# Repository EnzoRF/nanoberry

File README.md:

# Project Nanoberry*
(*) Provisional name until we find anything better

# What is it?
Nanoberry is a **single-board computer** capable of running **Linux**. It is built around the **i. MX 6 UltraLite** system-on-chip from NXP. It's **open-source hardware**, its design files are made in **KiCad** and it's free for everyone to produce it, sell it, modify it, and sell modified versions of it.

It is designed to be similar to the very popular **Raspberry PI**, with the same board size and connectors located in the same side. There are some differences, most notably it does not have HDMI output.

The goal is to have a small computer that everybody can modify according to their needs. All the electronics components can be purchased from electronics distributors and its operation is well documented by the manufacturers. This is the main difference with Raspberry PI.

All components are also available in industrial grade, for projects that require extra reliabilty with an increase in the cost. 

## License

You can modify this project and manufacture it, sell it for money, but you have to let me know.

    Nanoberry (provisional name). Open source single board computer.
    Copyright (C) 2020  vpecanins

    This program is free software: you can redistribute it and/or modify
    it under the terms of the GNU General Public License as published by
    the Free Software Foundation, either version 3 of the License, or
    (at your option) any later version.

    This program is distributed in the hope that it will be useful,
    but WITHOUT ANY WARRANTY; without even the implied warranty of
    MERCHANTABILITY or FITNESS FOR A PARTICULAR PURPOSE.  See the
    GNU General Public License for more details.

    You should have received a copy of the GNU General Public License
    along with this program.  If not, see <https://www.gnu.org/licenses/>.

 [GNU GENERAL PUBLIC LICENSE v3](https://www.gnu.org/licenses/gpl-3.0.en.html)

## Specifications

 - System-on-chip NXP i.MX 6 ULL:
	 - ARM Cortex A7 CPU at 900 MHz
	 - Yocto Linux Operating System
 - 4 layer PCB project made in KiCAD
 - Flash memory for program & data storage:
	 - Micro-SD card slot
	 - Onboard QSPI Flash (2 packages) for Bootloader and small OS
 - RAM memory: DDR3L one package
 - Display: 24-bit parallel RGB through bottom connector. (eLCDIF peripheral from i.MX6ULL)
	 - HDMI output would be nice but was discarded due to licensing costs and requirement of NDA does not follow the philosophy of this project.
 - Crypto memory A71CH from NXP to store private/public keys, just for fun because it's cheap.
 - PMIC PF1550 from NXP to generate needed voltages for CPU & memory
 - Ethernet 10/100 one port
 - USB to Serial port bridge for debugging and access Linux console
 - USB OTG port to implement special functions by i.MX (for example Mass Storage Device)
 - 4 port USB HUB to connect keyboard, mouse & other USB devices
 - Battery holder for RTC
 - Many I2C, SPI, I2S, UART, GPIO available through pin headers

## Block Diagram

## Status of the project

Hardware design is 99% done and has not been tested. We have based the design around a reference design from NXP. The most critical part of the layout, that is DDR3 routing, has been copied straight away from reference design.

Up to now this project has been brought up by a single person. This project cannot succeed without a team of people working on it. We need to check the schematics, refine layout, bring up the first prototype, boot Linux on it. If you are interested let me know.

We are also looking for funding/sponsors. NXP, we are using a lot of your chips here, if you are interested please show up now.

## BOM (critical components)

 1. MCIMX6Y2CVM08AB - System on chip Cortex A9 (NXP)
 2. MC34PF1550A6EP - PMIC (NXP)
 3. W634GU6MB - 512 MByte RAM (Winbond)
 4. CP2102N-A01-GQFN20 (SiLabs)
 5. LAN8720A-CP (Microchip)
 6. USB2514B (Microchip)

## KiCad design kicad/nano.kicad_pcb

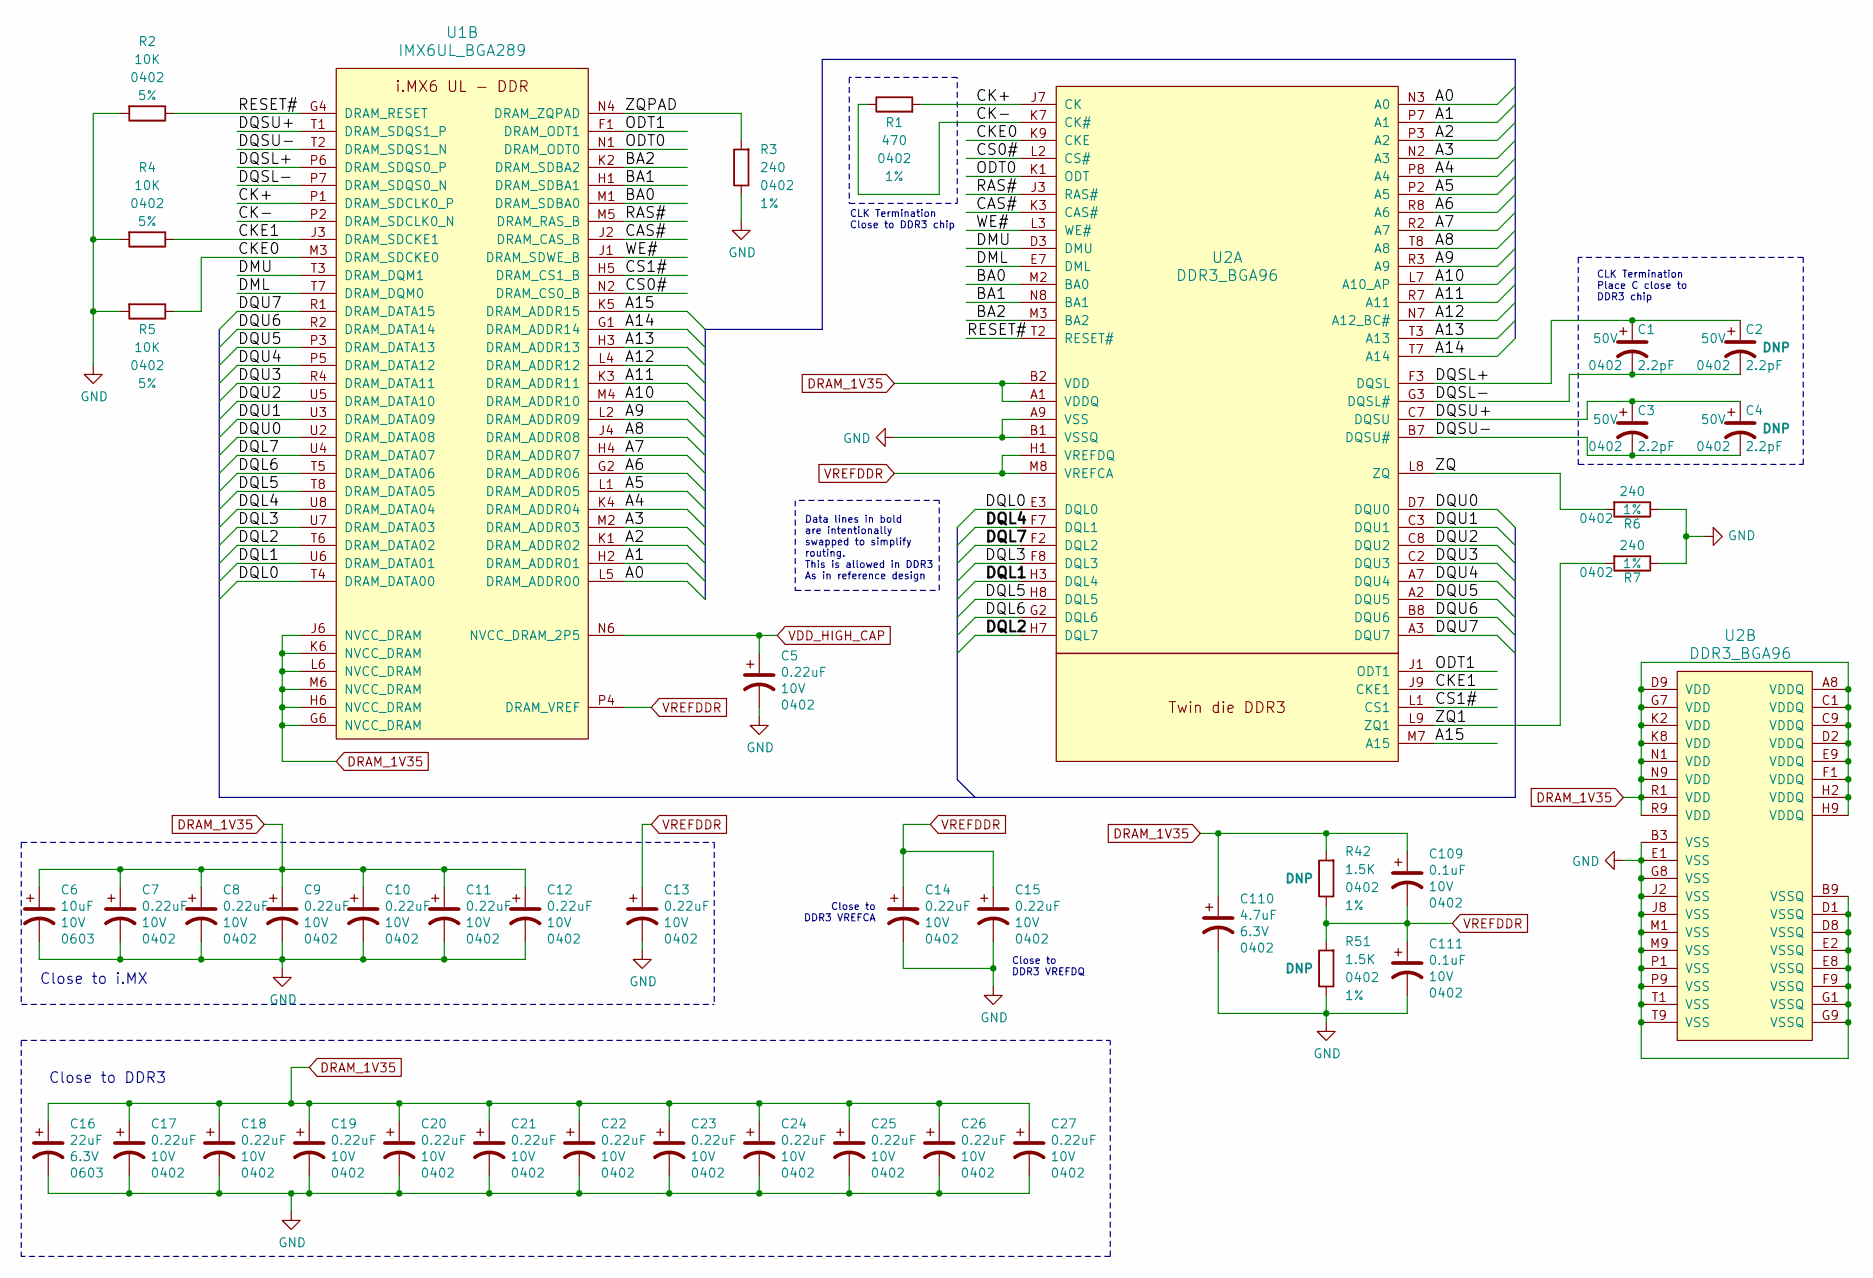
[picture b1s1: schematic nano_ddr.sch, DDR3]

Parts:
C1, C2, C3, C4: 2.2pF; C_0402_narrow; Voltage 50V
C5, C7, C8, C9, C10, C11, C12, C13, C14, C15, C17, C18, C19, C20, C21, C22, C23, C24, C25, C26, C27: 0.22uF; C_0402_narrow; Voltage 10V
C6: 10uF; C_0603_narrow; Voltage 10V
C16: 22uF; C_0603_narrow; Voltage 6.3V
C109, C111: 0.1uF; C_0402_narrow; Voltage 10V
C110: 4.7uF; C_0402_narrow; Voltage 6.3V
R1: 470; R_0402_narrow; Tolerance 1%
R2, R4, R5: 10K; R_0402_narrow; Tolerance 5%
R3, R6, R7: 240; R_0402_narrow; Tolerance 1%
R42, R51: 1.5K; R_0402_narrow; Tolerance 1%
U1: IMX6UL_BGA289
U2: DDR3_BGA96

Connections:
/DDR/A0: U1.L5 (DRAM_ADDR00), U2.N3 (A0)
/DDR/A1: U1.H2 (DRAM_ADDR01), U2.P7 (A1)
/DDR/A2: U1.K1 (DRAM_ADDR02), U2.P3 (A2)
/DDR/A3: U1.M2 (DRAM_ADDR03), U2.N2 (A3)
/DDR/A4: U1.K4 (DRAM_ADDR04), U2.P8 (A4)
/DDR/A5: U1.L1 (DRAM_ADDR05), U2.P2 (A5)
/DDR/A6: U1.G2 (DRAM_ADDR06), U2.R8 (A6)
/DDR/A7: U1.H4 (DRAM_ADDR07), U2.R2 (A7)
/DDR/A8: U1.J4 (DRAM_ADDR08), U2.T8 (A8)
/DDR/A9: U1.L2 (DRAM_ADDR09), U2.R3 (A9)
/DDR/A10: U1.M4 (DRAM_ADDR10), U2.L7 (A10_AP)
/DDR/A11: U1.K3 (DRAM_ADDR11), U2.R7 (A11)
/DDR/A12: U1.L4 (DRAM_ADDR12), U2.N7 (A12_BC#)
/DDR/A13: U1.H3 (DRAM_ADDR13), U2.T3 (A13)
/DDR/A14: U1.G1 (DRAM_ADDR14), U2.T7 (A14)
/DDR/A15: U1.K5 (DRAM_ADDR15), U2.M7 (A15)
/DDR/BA0: U1.M1 (DRAM_SDBA0), U2.M2 (BA0)
/DDR/BA1: U1.H1 (DRAM_SDBA1), U2.N8 (BA1)
/DDR/BA2: U1.K2 (DRAM_SDBA2), U2.M3 (BA2)
/DDR/CAS#: U1.J2 (DRAM_CAS_B), U2.K3 (CAS#)
/DDR/CK+: R1.2, U1.P1 (DRAM_SDCLK0_P), U2.J7 (CK)
/DDR/CK-: R1.1, U1.P2 (DRAM_SDCLK0_N), U2.K7 (CK#)
/DDR/CKE0: R5.1, U1.M3 (DRAM_SDCKE0), U2.K9 (CKE)
/DDR/CKE1: R4.1, U1.J3 (DRAM_SDCKE1), U2.J9 (CKE1)
/DDR/CS0#: U1.N2 (DRAM_CS0_B), U2.L2 (CS#)
/DDR/CS1#: U1.H5 (DRAM_CS1_B), U2.L1 (CS1)
/DDR/DML: U1.T7 (DRAM_DQM0), U2.E7 (DML)
/DDR/DMU: U1.T3 (DRAM_DQM1), U2.D3 (DMU)
/DDR/DQL0: U1.T4 (DRAM_DATA00), U2.E3 (DQL0)
/DDR/DQL1: U1.U6 (DRAM_DATA01), U2.H3 (DQL4)
/DDR/DQL2: U1.T6 (DRAM_DATA02), U2.H7 (DQL7)
/DDR/DQL3: U1.U7 (DRAM_DATA03), U2.F8 (DQL3)
/DDR/DQL4: U1.U8 (DRAM_DATA04), U2.F7 (DQL1)
/DDR/DQL5: U1.T8 (DRAM_DATA05), U2.H8 (DQL5)
/DDR/DQL6: U1.T5 (DRAM_DATA06), U2.G2 (DQL6)
/DDR/DQL7: U1.U4 (DRAM_DATA07), U2.F2 (DQL2)
/DDR/DQSL+: C1.1, C2.1, U1.P6 (DRAM_SDQS0_P), U2.F3 (DQSL)
/DDR/DQSL-: C1.2, C2.2, U1.P7 (DRAM_SDQS0_N), U2.G3 (DQSL#)
/DDR/DQSU+: C3.1, C4.1, U1.T1 (DRAM_SDQS1_P), U2.C7 (DQSU)
/DDR/DQSU-: C3.2, C4.2, U1.T2 (DRAM_SDQS1_N), U2.B7 (DQSU#)
/DDR/DQU0: U1.U2 (DRAM_DATA08), U2.D7 (DQU0)
/DDR/DQU1: U1.U3 (DRAM_DATA09), U2.C3 (DQU1)
/DDR/DQU2: U1.U5 (DRAM_DATA10), U2.C8 (DQU2)
/DDR/DQU3: U1.R4 (DRAM_DATA11), U2.C2 (DQU3)
/DDR/DQU4: U1.P5 (DRAM_DATA12), U2.A7 (DQU4)
/DDR/DQU5: U1.P3 (DRAM_DATA13), U2.A2 (DQU5)
/DDR/DQU6: U1.R2 (DRAM_DATA14), U2.B8 (DQU6)
/DDR/DQU7: U1.R1 (DRAM_DATA15), U2.A3 (DQU7)
/DDR/ODT0: U1.N1 (DRAM_ODT0), U2.K1 (ODT)
/DDR/ODT1: U1.F1 (DRAM_ODT1), U2.J1 (ODT1)
/DDR/RAS#: U1.M5 (DRAM_RAS_B), U2.J3 (RAS#)
/DDR/RESET#: R2.1, U1.G4 (DRAM_RESET), U2.T2 (RESET#)
/DDR/WE#: U1.J1 (DRAM_SDWE_B), U2.L3 (WE#)
/DDR/ZQ: R6.2, U2.L8 (ZQ)
/DDR/ZQ1: R7.2, U2.L9 (ZQ1)
/DDR/ZQPAD: R3.2, U1.N4 (DRAM_ZQPAD)
DRAM_1V35: C6.1, C7.1, C8.1, C9.1, C10.1, C11.1, C12.1, C16.1, C17.1, C18.1, C19.1, C20.1, C21.1, C22.1, C23.1, C24.1, C25.1, C26.1, C27.1, C109.1, C110.1, R42.2, U1.G6 (NVCC_DRAM), U1.H6 (NVCC_DRAM), U1.J6 (NVCC_DRAM), U1.K6 (NVCC_DRAM), U1.L6 (NVCC_DRAM), U1.M6 (NVCC_DRAM), U2.A1 (VDDQ), U2.A8 (VDDQ), U2.B2 (VDD), U2.C1 (VDDQ), U2.C9 (VDDQ), U2.D2 (VDDQ), U2.D9 (VDD), U2.E9 (VDDQ), U2.F1 (VDDQ), U2.G7 (VDD), U2.H2 (VDDQ), U2.H9 (VDDQ), U2.K2 (VDD), U2.K8 (VDD), U2.N1 (VDD), U2.N9 (VDD), U2.R1 (VDD), U2.R9 (VDD); also elsewhere on the board
GND: C5.2, C6.2, C7.2, C8.2, C9.2, C10.2, C11.2, C12.2, C13.2, C14.2, C15.2, C16.2, C17.2, C18.2, C19.2, C20.2, C21.2, C22.2, C23.2, C24.2, C25.2, C26.2, C27.2, C110.2, C111.2, R2.2, R3.1, R4.2, R5.2, R6.1, R7.1, R51.1, U2.A9 (VSS), U2.B1 (VSSQ), U2.B3 (VSS), U2.B9 (VSSQ), U2.D1 (VSSQ), U2.D8 (VSSQ), U2.E1 (VSS), U2.E2 (VSSQ), U2.E8 (VSSQ), U2.F9 (VSSQ), U2.G1 (VSSQ), U2.G8 (VSS), U2.G9 (VSSQ), U2.J2 (VSS), U2.J8 (VSS), U2.M1 (VSS), U2.M9 (VSS), U2.P1 (VSS), U2.P9 (VSS), U2.T1 (VSS), U2.T9 (VSS); also elsewhere on the board
VDD_HIGH_CAP: C5.1, U1.N6 (NVCC_DRAM_2P5); also elsewhere on the board
VREFDDR: C13.1, C14.1, C15.1, C109.2, C111.1, R42.1, R51.2, U1.P4 (DRAM_VREF), U2.H1 (VREFDQ), U2.M8 (VREFCA); also elsewhere on the board

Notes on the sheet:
CLK Termination Close to DDR3 chip
CLK Termination Place C close to DDR3 chip
Close to i.MX
Close to DDR3
Close to DDR3 VREFCA
Data lines in bold are intentionally swapped to simplify routing. This is allowed in DDR3 As in reference design
Close to DDR3 VREFDQ

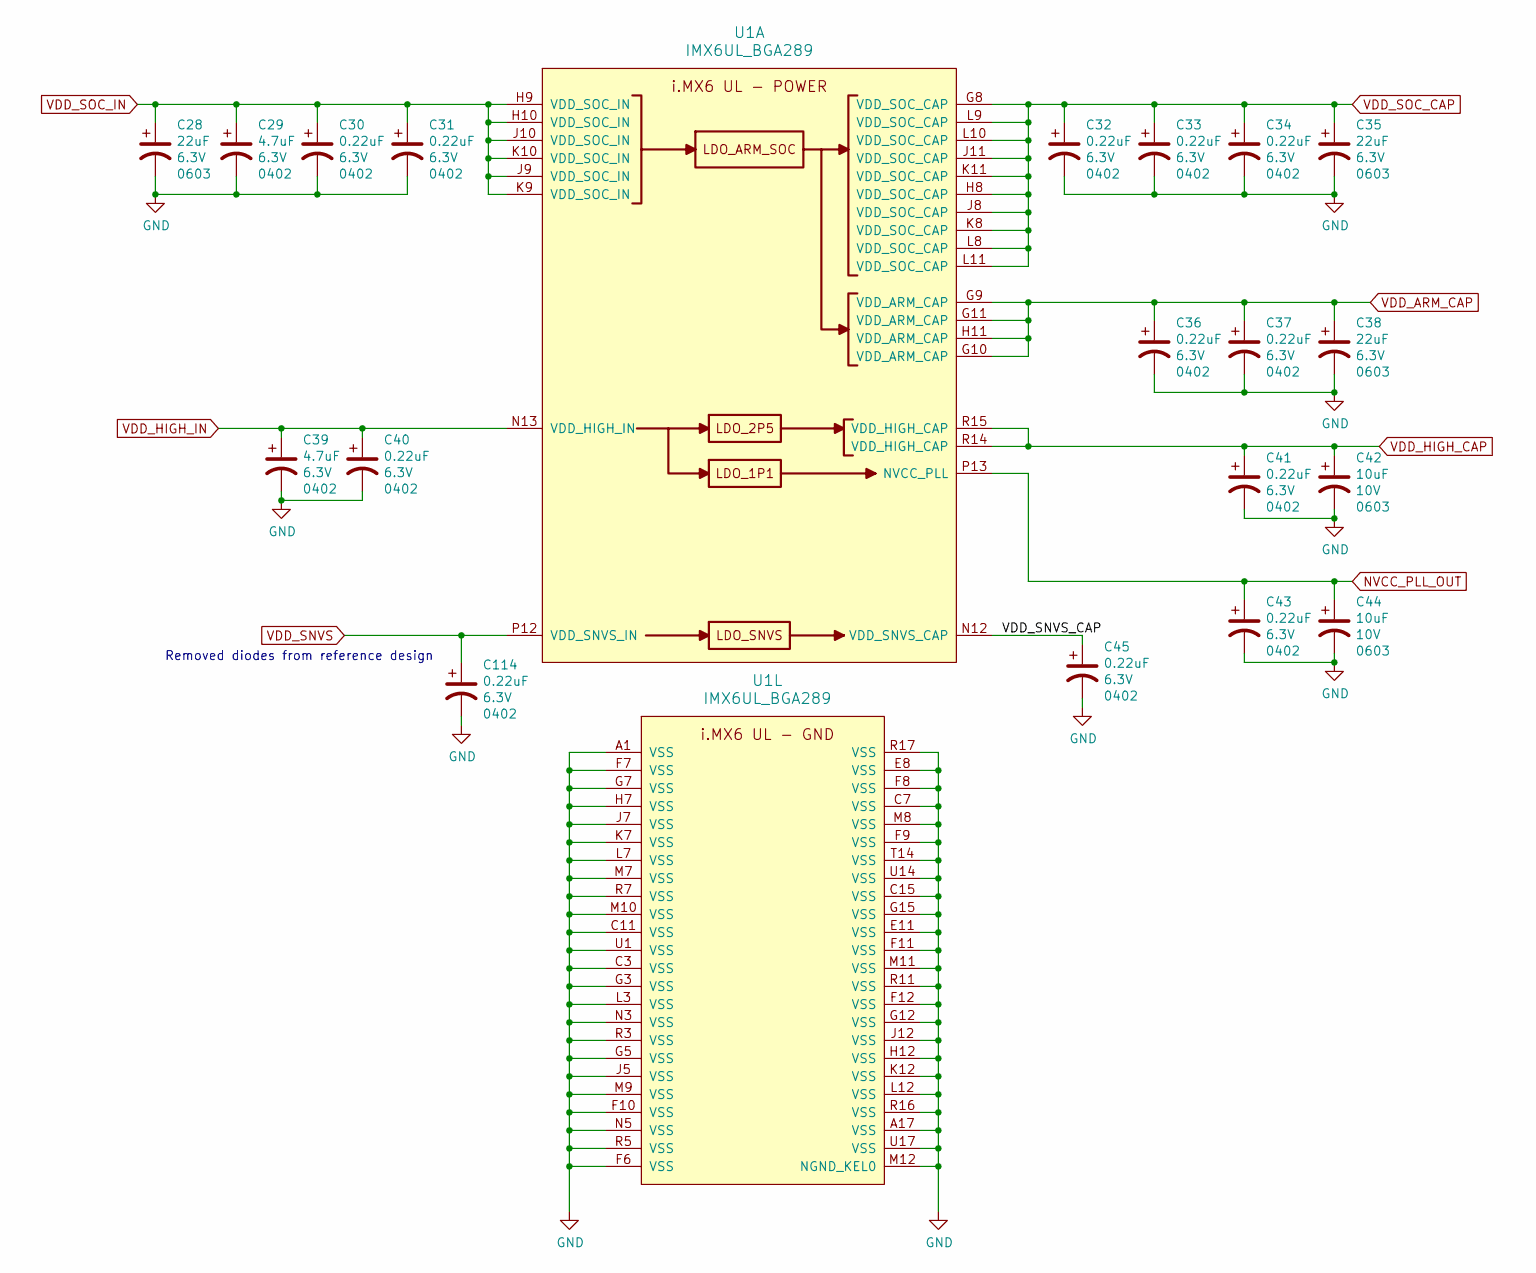
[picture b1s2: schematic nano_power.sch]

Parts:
C28, C35, C38: 22uF; C_0603_narrow; Voltage 6.3V
C29, C39: 4.7uF; C_0402_narrow; Voltage 6.3V
C30, C31, C32, C33, C34, C36, C37, C40, C41, C43, C45, C114: 0.22uF; C_0402_narrow; Voltage 6.3V
C42, C44: 10uF; C_0603_narrow; Voltage 10V
U1: IMX6UL_BGA289

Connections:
/IMX_Power_Pins/VDD_SNVS_CAP: C45.1, U1.N12 (VDD_SNVS_CAP)
GND: C28.2, C29.2, C30.2, C31.2, C32.2, C33.2, C34.2, C35.2, C36.2, C37.2, C38.2, C39.2, C40.2, C41.2, C42.2, C43.2, C44.2, C45.2, C114.2, U1.A1 (VSS), U1.A17 (VSS), U1.C3 (VSS), U1.C7 (VSS), U1.C11 (VSS), U1.C15 (VSS), U1.E8 (VSS), U1.E11 (VSS), U1.F6 (VSS), U1.F7 (VSS), U1.F8 (VSS), U1.F9 (VSS), U1.F10 (VSS), U1.F11 (VSS), U1.F12 (VSS), U1.G3 (VSS), U1.G5 (VSS), U1.G7 (VSS), U1.G12 (VSS), U1.G15 (VSS), U1.H7 (VSS), U1.H12 (VSS), U1.J5 (VSS), U1.J7 (VSS), U1.J12 (VSS), U1.K7 (VSS), U1.K12 (VSS), U1.L3 (VSS), U1.L7 (VSS), U1.L12 (VSS), U1.M7 (VSS), U1.M8 (VSS), U1.M9 (VSS), U1.M10 (VSS), U1.M11 (VSS), U1.M12 (NGND_KEL0), U1.N3 (VSS), U1.N5 (VSS), U1.R3 (VSS), U1.R5 (VSS), U1.R7 (VSS), U1.R11 (VSS), U1.R16 (VSS), U1.R17 (VSS), U1.T14 (VSS), U1.U1 (VSS), U1.U14 (VSS), U1.U17 (VSS); also elsewhere on the board
NVCC_PLL_OUT: C43.1, C44.1, U1.P13 (NVCC_PLL)
VDD_ARM_CAP: C36.1, C37.1, C38.1, U1.G9 (VDD_ARM_CAP), U1.G10 (VDD_ARM_CAP), U1.G11 (VDD_ARM_CAP), U1.H11 (VDD_ARM_CAP)
VDD_HIGH_CAP: C41.1, C42.1, U1.R14 (VDD_HIGH_CAP), U1.R15 (VDD_HIGH_CAP); also elsewhere on the board
VDD_HIGH_IN: C39.1, C40.1, U1.N13 (VDD_HIGH_IN); also elsewhere on the board
VDD_SNVS: C114.1, U1.P12 (VDD_SNVS_IN); also elsewhere on the board
VDD_SOC_CAP: C32.1, C33.1, C34.1, C35.1, U1.G8 (VDD_SOC_CAP), U1.H8 (VDD_SOC_CAP), U1.J8 (VDD_SOC_CAP), U1.J11 (VDD_SOC_CAP), U1.K8 (VDD_SOC_CAP), U1.K11 (VDD_SOC_CAP), U1.L8 (VDD_SOC_CAP), U1.L9 (VDD_SOC_CAP), U1.L10 (VDD_SOC_CAP), U1.L11 (VDD_SOC_CAP)
VDD_SOC_IN: C28.1, C29.1, C30.1, C31.1, U1.H9 (VDD_SOC_IN), U1.H10 (VDD_SOC_IN), U1.J9 (VDD_SOC_IN), U1.J10 (VDD_SOC_IN), U1.K9 (VDD_SOC_IN), U1.K10 (VDD_SOC_IN); also elsewhere on the board

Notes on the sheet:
Removed diodes from reference design

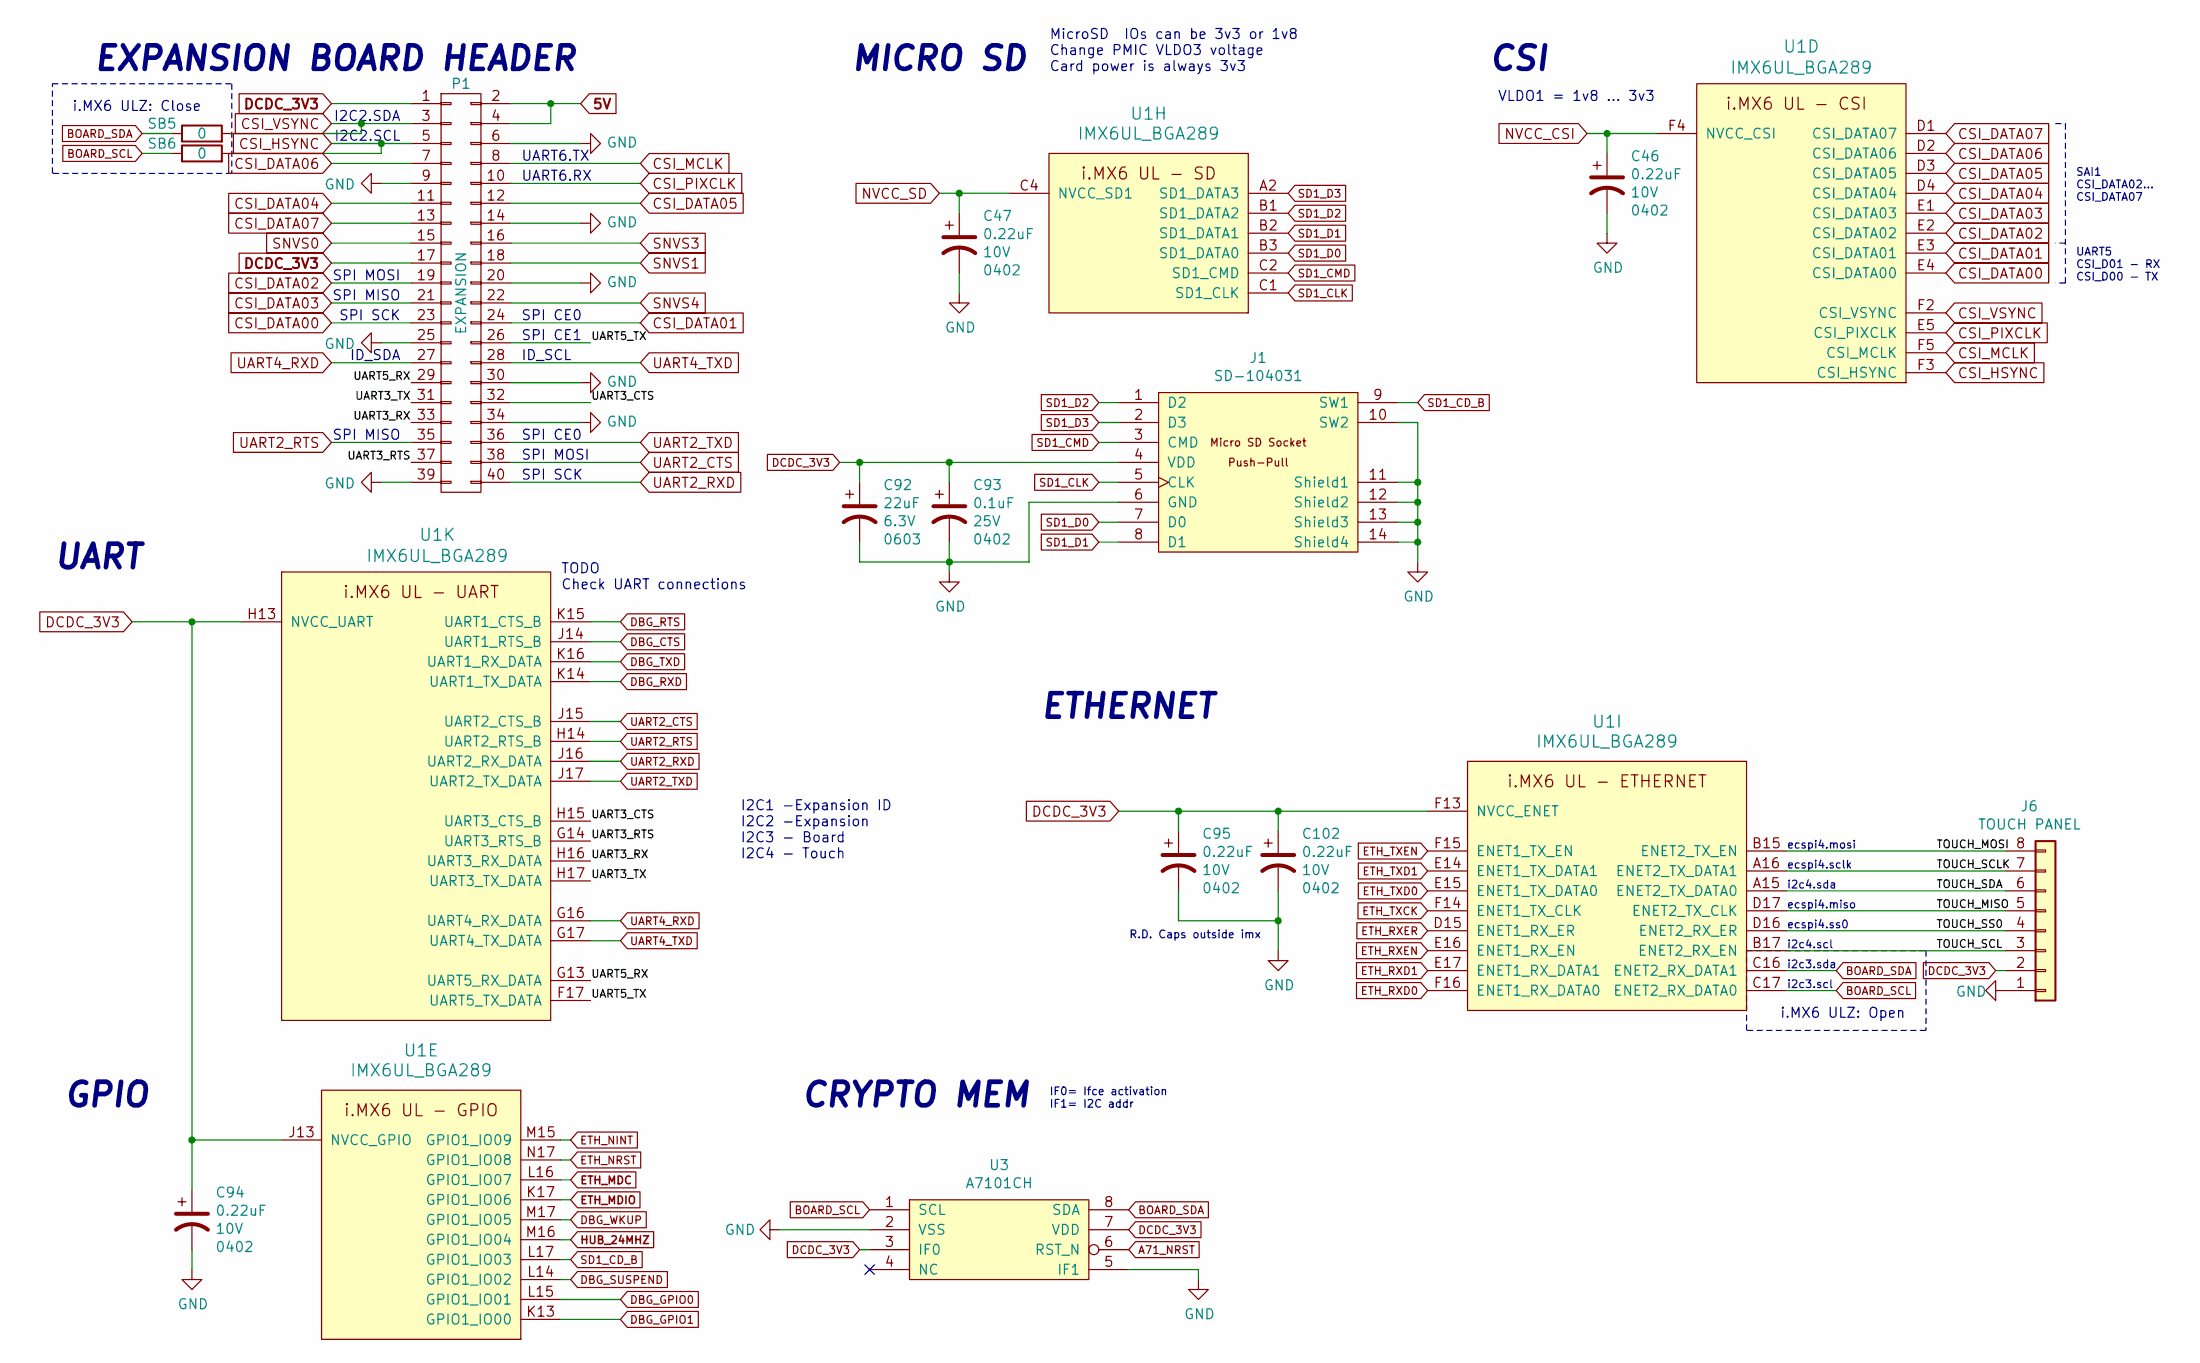
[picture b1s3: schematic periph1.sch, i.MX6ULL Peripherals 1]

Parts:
C46, C47, C94, C95, C102: 0.22uF; C_0402_narrow; Voltage 10V
C92: 22uF; C_0603_narrow; Voltage 6.3V
C93: 0.1uF; C_0402_narrow; Voltage 25V
J1: SD-104031; uSD_104031
J6: TOUCH PANEL; PinHeader_1x08_P2.54mm_Vertical
P1: EXPANSION; PINHD_2X20_X
SB5, SB6: 0; R_0402_narrow; Tolerance ?
U1: IMX6UL_BGA289
U3: A7101CH; SOT909-1

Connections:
5V: P1.2, P1.4; also elsewhere on the board
/IMX_Peripherals_1/TOUCH_MISO: J6.5, U1.D17 (ENET2_TX_CLK)
/IMX_Peripherals_1/TOUCH_MOSI: J6.8, U1.B15 (ENET2_TX_EN)
/IMX_Peripherals_1/TOUCH_SCL: J6.3, U1.B17 (ENET2_RX_EN)
/IMX_Peripherals_1/TOUCH_SCLK: J6.7, U1.A16 (ENET2_TX_DATA1)
/IMX_Peripherals_1/TOUCH_SDA: J6.6, U1.A15 (ENET2_TX_DATA0)
/IMX_Peripherals_1/TOUCH_SS0: J6.4, U1.D16 (ENET2_RX_ER)
/IMX_Peripherals_1/UART3_CTS: P1.32, U1.H15 (UART3_CTS_B)
/IMX_Peripherals_1/UART3_RTS: P1.37, U1.G14 (UART3_RTS_B)
/IMX_Peripherals_1/UART3_RX: P1.33, U1.H16 (UART3_RX_DATA)
/IMX_Peripherals_1/UART3_TX: P1.31, U1.H17 (UART3_TX_DATA)
/IMX_Peripherals_1/UART5_RX: P1.29, U1.G13 (UART5_RX_DATA)
/IMX_Peripherals_1/UART5_TX: P1.26, U1.F17 (UART5_TX_DATA)
A71_NRST: U3.6 (RST_N); also elsewhere on the board
BOARD_SCL: SB6.1, U1.C17 (ENET2_RX_DATA0), U3.1 (SCL); also elsewhere on the board
BOARD_SDA: SB5.1, U1.C16 (ENET2_RX_DATA1), U3.8 (SDA); also elsewhere on the board
CSI_DATA00: P1.23, U1.E4 (CSI_DATA00)
CSI_DATA01: P1.24, U1.E3 (CSI_DATA01)
CSI_DATA02: P1.19, U1.E2 (CSI_DATA02)
CSI_DATA03: P1.21, U1.E1 (CSI_DATA03)
CSI_DATA04: P1.11, U1.D4 (CSI_DATA04)
CSI_DATA05: P1.12, U1.D3 (CSI_DATA05)
CSI_DATA06: P1.7, U1.D2 (CSI_DATA06)
CSI_DATA07: P1.13, U1.D1 (CSI_DATA07)
CSI_HSYNC: P1.5, SB6.2, U1.F3 (CSI_HSYNC)
CSI_MCLK: P1.8, U1.F5 (CSI_MCLK)
CSI_PIXCLK: P1.10, U1.E5 (CSI_PIXCLK)
CSI_VSYNC: P1.3, SB5.2, U1.F2 (CSI_VSYNC)
DBG_CTS: U1.J14 (UART1_RTS_B); also elsewhere on the board
DBG_GPIO0: U1.L15 (GPIO1_IO01); also elsewhere on the board
DBG_GPIO1: U1.K13 (GPIO1_IO00); also elsewhere on the board
DBG_RTS: U1.K15 (UART1_CTS_B); also elsewhere on the board
DBG_RXD: U1.K14 (UART1_TX_DATA); also elsewhere on the board
DBG_SUSPEND: U1.L14 (GPIO1_IO02); also elsewhere on the board
DBG_TXD: U1.K16 (UART1_RX_DATA); also elsewhere on the board
DBG_WKUP: U1.M17 (GPIO1_IO05); also elsewhere on the board
DCDC_3V3: C92.1, C93.1, C94.1, C95.1, C102.1, J1.4 (VDD), J6.2, P1.1, P1.17, U1.F13 (NVCC_ENET), U1.H13 (NVCC_UART), U1.J13 (NVCC_GPIO), U3.3 (IF0), U3.7 (VDD); also elsewhere on the board
ETH_MDC: U1.L16 (GPIO1_IO07); also elsewhere on the board
ETH_MDIO: U1.K17 (GPIO1_IO06); also elsewhere on the board
ETH_NINT: U1.M15 (GPIO1_IO09); also elsewhere on the board
ETH_NRST: U1.N17 (GPIO1_IO08); also elsewhere on the board
ETH_RXD0: U1.F16 (ENET1_RX_DATA0); also elsewhere on the board
ETH_RXD1: U1.E17 (ENET1_RX_DATA1); also elsewhere on the board
ETH_RXEN: U1.E16 (ENET1_RX_EN); also elsewhere on the board
ETH_RXER: U1.D15 (ENET1_RX_ER); also elsewhere on the board
ETH_TXCK: U1.F14 (ENET1_TX_CLK); also elsewhere on the board
ETH_TXD0: U1.E15 (ENET1_TX_DATA0); also elsewhere on the board
ETH_TXD1: U1.E14 (ENET1_TX_DATA1); also elsewhere on the board
ETH_TXEN: U1.F15 (ENET1_TX_EN); also elsewhere on the board
GND: C46.2, C47.2, C92.2, C93.2, C94.2, C95.2, C102.2, J1.6 (GND), J1.10 (SW2), J1.11 (Shield1), J1.12 (Shield2), J1.13 (Shield3), J1.14 (Shield4), J6.1, P1.6, P1.9, P1.14, P1.20, P1.25, P1.30, P1.34, P1.39, U3.2 (VSS), U3.5 (IF1); also elsewhere on the board
HUB_24MHZ: U1.M16 (GPIO1_IO04); also elsewhere on the board
NVCC_CSI: C46.1, U1.F4 (NVCC_CSI); also elsewhere on the board
NVCC_SD: C47.1, U1.C4 (NVCC_SD1); also elsewhere on the board
SD1_CD_B: J1.9 (SW1), U1.L17 (GPIO1_IO03)
SD1_CLK: J1.5 (CLK), U1.C1 (SD1_CLK)
SD1_CMD: J1.3 (CMD), U1.C2 (SD1_CMD)
SD1_D0: J1.7 (D0), U1.B3 (SD1_DATA0)
SD1_D1: J1.8 (D1), U1.B2 (SD1_DATA1)
SD1_D2: J1.1 (D2), U1.B1 (SD1_DATA2)
SD1_D3: J1.2 (D3), U1.A2 (SD1_DATA3)
SNVS0: P1.15; also elsewhere on the board
SNVS1: P1.18; also elsewhere on the board
SNVS3: P1.16; also elsewhere on the board
SNVS4: P1.22; also elsewhere on the board
UART2_CTS: P1.38, U1.J15 (UART2_CTS_B)
UART2_RTS: P1.35, U1.H14 (UART2_RTS_B)
UART2_RXD: P1.40, U1.J16 (UART2_RX_DATA)
UART2_TXD: P1.36, U1.J17 (UART2_TX_DATA)
UART4_RXD: P1.27, U1.G16 (UART4_RX_DATA)
UART4_TXD: P1.28, U1.G17 (UART4_TX_DATA)

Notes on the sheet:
TODO Check UART connections
ETHERNET
UART
EXPANSION BOARD HEADER
MICRO SD
I2C2.SDA
I2C2.SCL
UART6.TX
UART6.RX
SPI MOSI
SPI MISO
SPI SCK
SPI CE0
SPI CE1
ID_SDA
ID_SCL
CSI
CRYPTO MEM
GPIO
MicroSD IOs can be 3v3 or 1v8 Change PMIC VLDO3 voltage Card power is always 3v3
SAI1 CSI_DATA02... CSI_DATA07
UART5 CSI_D01 - RX CSI_D00 - TX
VLDO1 = 1v8 ... 3v3
IF0= Ifce activation IF1= I2C addr
i2c4.sda
i2c4.scl
i2c3.sda
i2c3.scl
I2C1 -Expansion ID I2C2 -Expansion I2C3 - Board I2C4 - Touch
ecspi4.mosi
ecspi4.sclk
ecspi4.miso
ecspi4.ss0
R.D. Caps outside imx
i.MX6 ULZ: Close
i.MX6 ULZ: Open

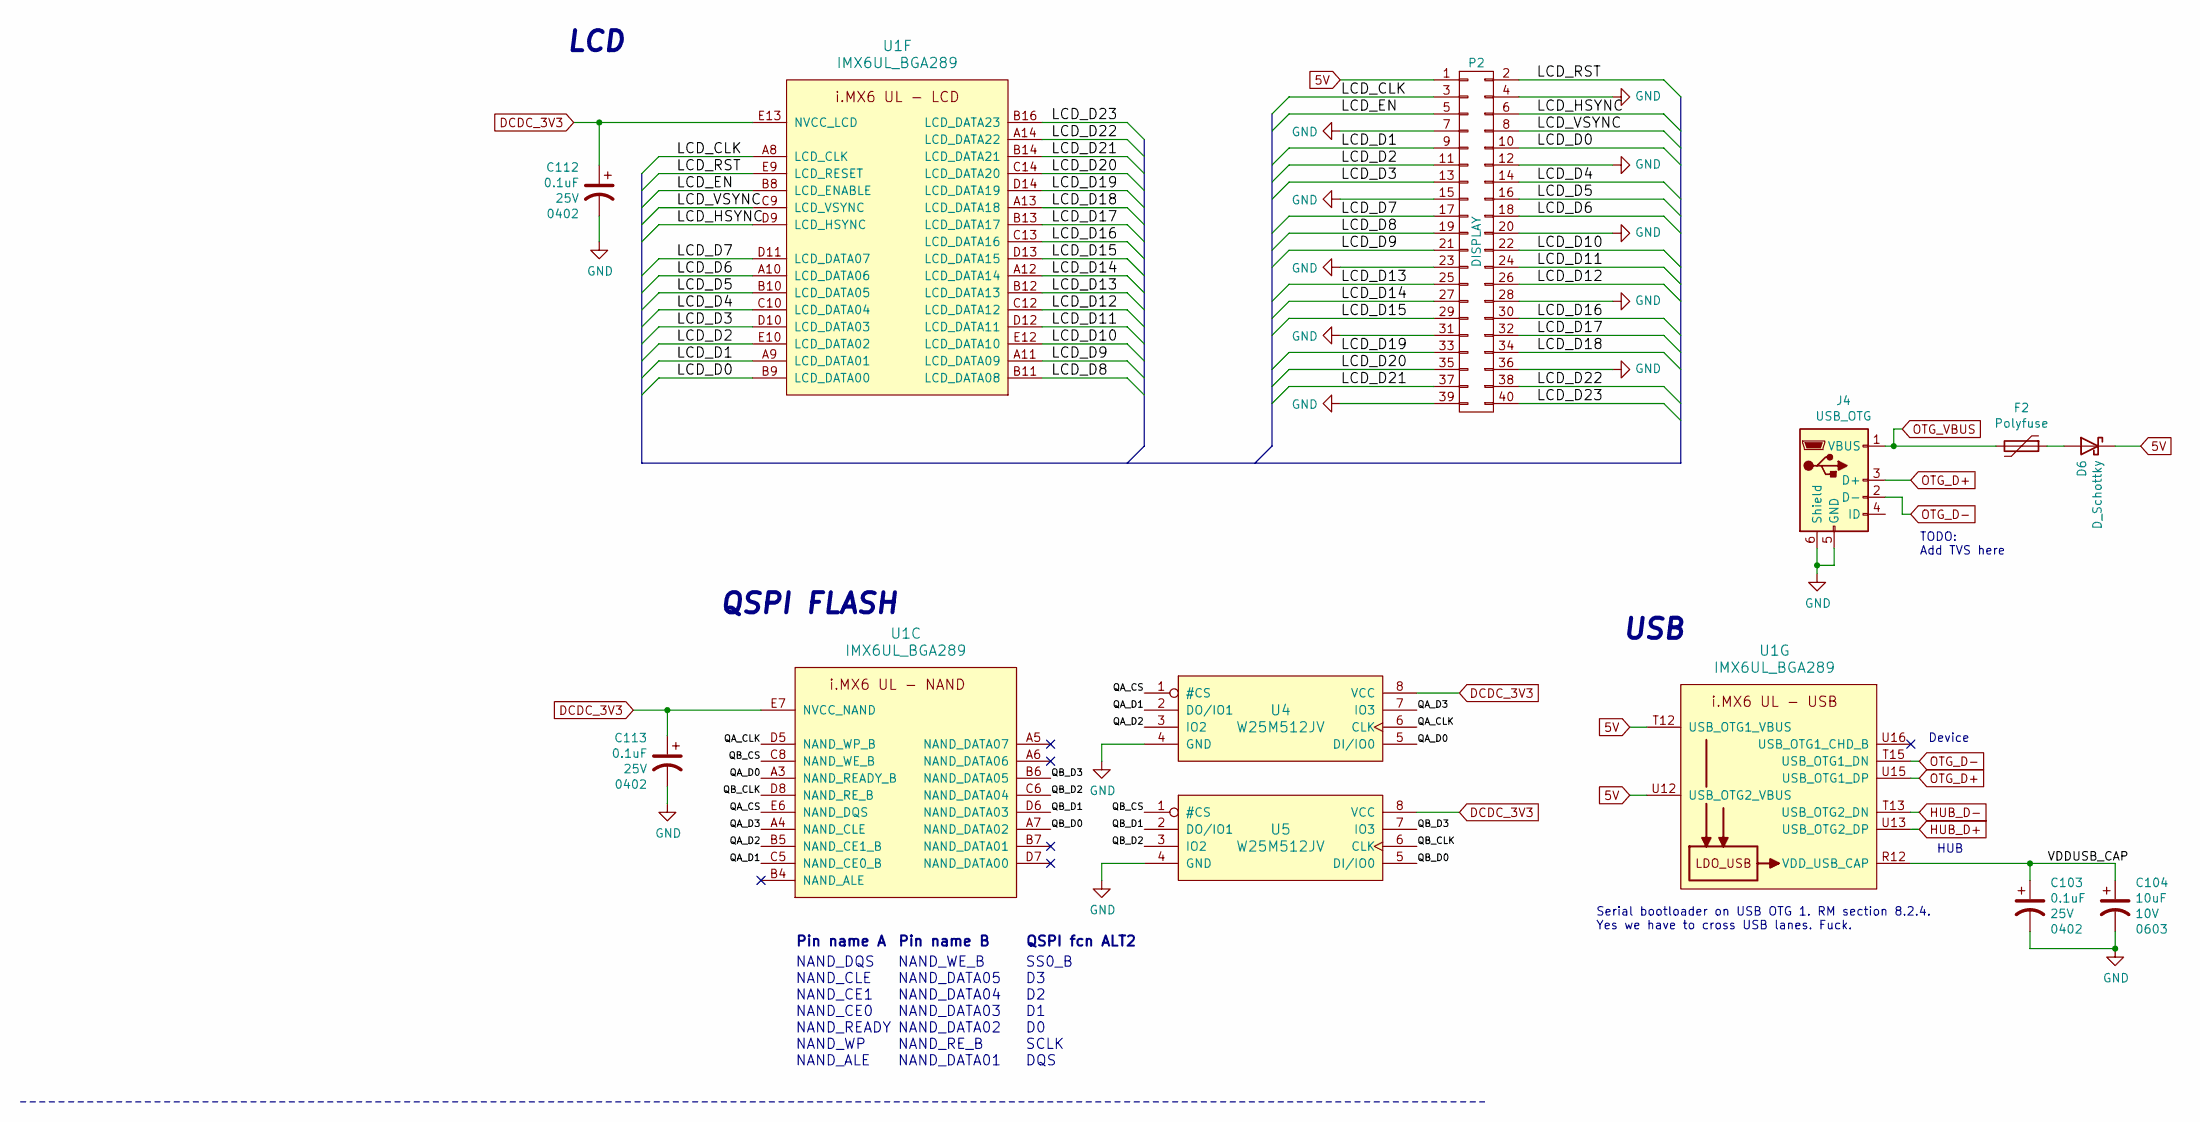
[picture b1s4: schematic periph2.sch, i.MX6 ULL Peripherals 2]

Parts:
C103, C112, C113: 0.1uF; C_0402_narrow; Voltage 25V
C104: 10uF; C_0603_narrow; Voltage 10V
D6: D_Schottky; D_0805_2012Metric
F2: Polyfuse; D_0805_2012Metric
J4: USB_OTG; MCR-B-S-RA-SMT-CS5
P2: DISPLAY; PINHD_2X20_X
U1: IMX6UL_BGA289
U4, U5: W25M512JV; WSON8_8x6mm

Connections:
5V: D6.1 (K), P2.1, U1.T12 (USB_OTG1_VBUS), U1.U12 (USB_OTG2_VBUS); also elsewhere on the board
/IMX_Peripherals_2/LCD_CLK: P2.3, U1.A8 (LCD_CLK)
/IMX_Peripherals_2/LCD_D0: P2.10, U1.B9 (LCD_DATA00)
/IMX_Peripherals_2/LCD_D1: P2.9, U1.A9 (LCD_DATA01)
/IMX_Peripherals_2/LCD_D2: P2.11, U1.E10 (LCD_DATA02)
/IMX_Peripherals_2/LCD_D3: P2.13, U1.D10 (LCD_DATA03)
/IMX_Peripherals_2/LCD_D4: P2.14, U1.C10 (LCD_DATA04)
/IMX_Peripherals_2/LCD_D5: P2.16, U1.B10 (LCD_DATA05)
/IMX_Peripherals_2/LCD_D6: P2.18, U1.A10 (LCD_DATA06)
/IMX_Peripherals_2/LCD_D7: P2.17, U1.D11 (LCD_DATA07)
/IMX_Peripherals_2/LCD_D8: P2.19, U1.B11 (LCD_DATA08)
/IMX_Peripherals_2/LCD_D9: P2.21, U1.A11 (LCD_DATA09)
/IMX_Peripherals_2/LCD_D10: P2.22, U1.E12 (LCD_DATA10)
/IMX_Peripherals_2/LCD_D11: P2.24, U1.D12 (LCD_DATA11)
/IMX_Peripherals_2/LCD_D12: P2.26, U1.C12 (LCD_DATA12)
/IMX_Peripherals_2/LCD_D13: P2.25, U1.B12 (LCD_DATA13)
/IMX_Peripherals_2/LCD_D14: P2.27, U1.A12 (LCD_DATA14)
/IMX_Peripherals_2/LCD_D15: P2.29, U1.D13 (LCD_DATA15)
/IMX_Peripherals_2/LCD_D16: P2.30, U1.C13 (LCD_DATA16)
/IMX_Peripherals_2/LCD_D17: P2.32, U1.B13 (LCD_DATA17)
/IMX_Peripherals_2/LCD_D18: P2.34, U1.A13 (LCD_DATA18)
/IMX_Peripherals_2/LCD_D19: P2.33, U1.D14 (LCD_DATA19)
/IMX_Peripherals_2/LCD_D20: P2.35, U1.C14 (LCD_DATA20)
/IMX_Peripherals_2/LCD_D21: P2.37, U1.B14 (LCD_DATA21)
/IMX_Peripherals_2/LCD_D22: P2.38, U1.A14 (LCD_DATA22)
/IMX_Peripherals_2/LCD_D23: P2.40, U1.B16 (LCD_DATA23)
/IMX_Peripherals_2/LCD_EN: P2.5, U1.B8 (LCD_ENABLE)
/IMX_Peripherals_2/LCD_HSYNC: P2.6, U1.D9 (LCD_HSYNC)
/IMX_Peripherals_2/LCD_RST: P2.2, U1.E9 (LCD_RESET)
/IMX_Peripherals_2/LCD_VSYNC: P2.8, U1.C9 (LCD_VSYNC)
/IMX_Peripherals_2/QA_CLK: U1.D5 (NAND_WP_B), U4.6 (CLK)
/IMX_Peripherals_2/QA_CS: U1.E6 (NAND_DQS), U4.1 (#CS)
/IMX_Peripherals_2/QA_D0: U1.A3 (NAND_READY_B), U4.5 (DI/IO0)
/IMX_Peripherals_2/QA_D1: U1.C5 (NAND_CE0_B), U4.2 (DO/IO1)
/IMX_Peripherals_2/QA_D2: U1.B5 (NAND_CE1_B), U4.3 (IO2)
/IMX_Peripherals_2/QA_D3: U1.A4 (NAND_CLE), U4.7 (IO3)
/IMX_Peripherals_2/QB_CLK: U1.D8 (NAND_RE_B), U5.6 (CLK)
/IMX_Peripherals_2/QB_CS: U1.C8 (NAND_WE_B), U5.1 (#CS)
/IMX_Peripherals_2/QB_D0: U1.A7 (NAND_DATA02), U5.5 (DI/IO0)
/IMX_Peripherals_2/QB_D1: U1.D6 (NAND_DATA03), U5.2 (DO/IO1)
/IMX_Peripherals_2/QB_D2: U1.C6 (NAND_DATA04), U5.3 (IO2)
/IMX_Peripherals_2/QB_D3: U1.B6 (NAND_DATA05), U5.7 (IO3)
/IMX_Peripherals_2/VDDUSB_CAP: C103.1, C104.1, U1.R12 (VDD_USB_CAP)
DCDC_3V3: C112.1, C113.1, U1.E7 (NVCC_NAND), U1.E13 (NVCC_LCD), U4.8 (VCC), U5.8 (VCC); also elsewhere on the board
GND: C103.2, C104.2, C112.2, C113.2, J4.5 (GND), J4.6 (Shield), P2.4, P2.7, P2.12, P2.15, P2.20, P2.23, P2.28, P2.31, P2.36, P2.39, U4.4 (GND), U5.4 (GND); also elsewhere on the board
HUB_D+: U1.U13 (USB_OTG2_DP); also elsewhere on the board
HUB_D-: U1.T13 (USB_OTG2_DN); also elsewhere on the board
unnamed: D6.2 (A), F2.1
OTG_D+: J4.3 (D+), U1.U15 (USB_OTG1_DP)
OTG_D-: J4.2 (D-), U1.T15 (USB_OTG1_DN)
OTG_VBUS: F2.2, J4.1 (VBUS)

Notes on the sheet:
NAND_DQS NAND_CLE NAND_CE1 NAND_CE0 NAND_READY NAND_WP NAND_ALE
SS0_B D3 D2 D1 D0 SCLK DQS
Pin name A
QSPI fcn ALT2
QSPI FLASH
Pin name B
NAND_WE_B NAND_DATA05 NAND_DATA04 NAND_DATA03 NAND_DATA02 NAND_RE_B NAND_DATA01
USB
HUB
Device
Serial bootloader on USB OTG 1. RM section 8.2.4. Yes we have to cross USB lanes. Fuck.
LCD
TODO: Add TVS here
